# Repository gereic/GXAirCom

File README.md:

# GxAirCom

GxAircom aims to be a complete and open source implementation of the [FANET+ (Fanet + Flarm) protocol](https://github.com/3s1d/fanet-stm32/blob/master/Src/fanet/radio/protocol.txt) running on readily available cheap lora modules and interfacing with mobile phones via Bluetooth. It can also act as a Fanet ground station and broadcast recieved FANET information to [OGN](http://wiki.glidernet.org).

For information and documentation see:

- [The PDF quick guide](doc/20200908%20-%20GXAirCom%20-%20Quick%20Guide.pdf) and the [The PDF Documentation](doc/20200723%20-%20GXAirCom%20-%20A%20LoRa%20communication%20device%20for%20free%20flying.pdf)
- Further information can be found in [the wiki](https://github.com/gereic/GXAirCom/wiki) and [the docs folder](doc/). E.g.:
    - [The list of supported hardware](https://github.com/gereic/GXAirCom/wiki/Hardware-supported)
    - [The list of supported smartphone software](https://github.com/gereic/GXAirCom/wiki/Software)
    - [How to update the firmware](https://github.com/gereic/GXAirCom/wiki/Upgrading---updating-the-firmware-using-the-internal-web-interface-and-a-cellphone)
    - [See the video tutorials](https://github.com/gereic/GXAirCom/wiki/Video-Tutorials)

## ADS-L (SRD-860 M-Band) Support

GXAirCom implements the EASA **ADS-L 4 SRD-860** iConspicuity protocol (Issue 1 / Issue 2, December 2025).  
ADS-L lets non-certified aircraft broadcast and receive position data on a standardised EU frequency plan, independently of FLARM.

### Protocol overview

| Parameter | Value |
|---|---|
| Frequencies | 868.200 MHz and 868.400 MHz (M-Band), alternated per transmission |
| Modulation | 2-GFSK, 100 kbps chip rate (50 kbps net after Manchester) |
| Deviation | ±50 kHz |
| RX bandwidth | 125 kHz |
| Encoding | Software Manchester — G.E. Thomas convention (`0`→`10`, `1`→`01`) |
| Hardware Manchester | Disabled (`RegPacketConfig1 = 0x00`) |

### Packet structure (25 decoded bytes)

```
Byte  0      Length byte = 0x18 (24 bytes follow)
Byte  1      Network byte: Protocol=0, SigFlag=0, KeyIdx=0, ECM=0
Bytes 2–21   ADS-L Data (20 bytes) — XXTEA-scrambled
               Byte  2     Payload Type = 0x02 (Traffic / iConspicuity)
               Bytes 3–5   Sender address (24-bit, MSB first)
               Byte  6     AMT (6 bits, bits[7:2]) | Relay (bit 0)
               Bytes 7–21  iConspicuity payload (15 bytes = 120 bits)
Bytes 22–24  CRC-24 (big-endian, covers bytes 1–21)
```

On air the 25-byte packet is Manchester-encoded to **50 bytes**, transmitted after the sync word.

### iConspicuity payload bit layout (120 bits, MSB-first)

| Bits | Width | Field | Unit / notes |
|---|---|---|---|
| 0–5 | 6 | Timestamp | Quarter-seconds since UTC hour, mod 60 (0–59) |
| 6–7 | 2 | Flight State | 0=undefined, 1=ground, 2=airborne |
| 8–12 | 5 | Aircraft Category | 0=none … 13=UAS certified (EASA Issue 2 table) |
| 13–15 | 3 | Emergency Status | 0=none, 2=general, 3=medical … |
| 16–39 | 24 | Latitude | Signed, LSB = 1°/93 206 (~1.2 m) |
| 40–63 | 24 | Longitude | Signed, LSB = 1°/46 603 (~1.2 m at equator) |
| 64–71 | 8 | Ground Speed | Exp-unsigned N=6, unit 0.25 m/s |
| 72–85 | 14 | Altitude WGS-84 | Exp-unsigned N=12, +320 m offset |
| 86–94 | 9 | Vertical Rate | Exp-signed N=6, unit 0.125 m/s (sign in bit 8) |
| 95–103 | 9 | Ground Track | Cyclic, 360°/512 per LSB |
| 104–105 | 2 | SIL | Source Integrity Level |
| 106–107 | 2 | DAL | Design Assurance Level |
| 108–111 | 4 | NIC | Navigation Integrity Category |
| 112–114 | 3 | HFOM | Horizontal Figure of Merit |
| 115–116 | 2 | VFOM | Vertical Figure of Merit |
| 117–118 | 2 | NACv | Navigation Accuracy for Velocity |
| 119 | 1 | Reserved | Always 0 |

Non-certified devices transmit SIL=0, DAL=0 (conservative defaults per spec appendix).

### Scrambling — XXTEA

ADS-L Data (bytes 2–21, 20 bytes = 5 × uint32\_t LE words) is scrambled with **XXTEA**, 6 rounds, all-zero 128-bit key.  
This provides basic obfuscation but not cryptographic security (the spec acknowledges this).

### CRC-24

Same polynomial as Mode-S / ADS-B: **0xFFFA0480** (generator degree 24).  
The CRC is computed over 21 bytes (Network byte + XXTEA-encrypted ADS-L Data) and appended big-endian.

### Sync word

The radio sync word is a **6-byte Manchester-encoded** pattern derived from raw bytes `0xF5 0x72 0x4B`:

```
55 99 95 A6 9A 65
```

This 6-byte form matches the **OpenACE** and **SoftRF** on-air pattern.  
The leading `55 99` = Manchester(`0xF5`) acts as the explicit preamble byte required on SX1262 hardware (see [issue #210](https://github.com/gereic/GXAirCom/issues/210)).  
The spec-defined sync bytes `0x72 0x4B` are encoded as `95 A6 9A 65`.

| Chip | Sync config | SyncWordLength |
|---|---|---|
| SX1276 | `RegSyncConfig = 0x35` (SyncOn, SyncSize=6) | 6 bytes |
| SX1262 | SetPacketParams, 48 bits | 6 bytes written to register `0x06C0` |

### Address Mapping Table (AMT)

GXAirCom uses AMT = **8 (FANET)** by default. Other notable values: 5=ICAO, 6=FLARM, 7=OGN, 0=Random/Privacy.

### Interoperability

| System | Status |
|---|---|
| OpenACE | ✅ Compatible — same 6-byte sync, same packet structure |
| SoftRF (moshe-braner fork) | ✅ Compatible — same sync word pattern confirmed |
| OGN receivers | ✅ CRC-24 + packet structure matches Mode-S tooling |

Similar/ related projects are:

- The [SoftRF](https://github.com/lyusupov/SoftRF) project, which has wider hardware and protocol support, but implements only the subset of the FANET protocol that broadcasts and receives locations. It also cannot broadcast FANET and FLARM at the same time.
- The [Skytraxx FANET Source](https://github.com/3s1d/fanet-stm32). The original reference implementation of the FANET standard and upstream of the standard protocol specification and documentation.

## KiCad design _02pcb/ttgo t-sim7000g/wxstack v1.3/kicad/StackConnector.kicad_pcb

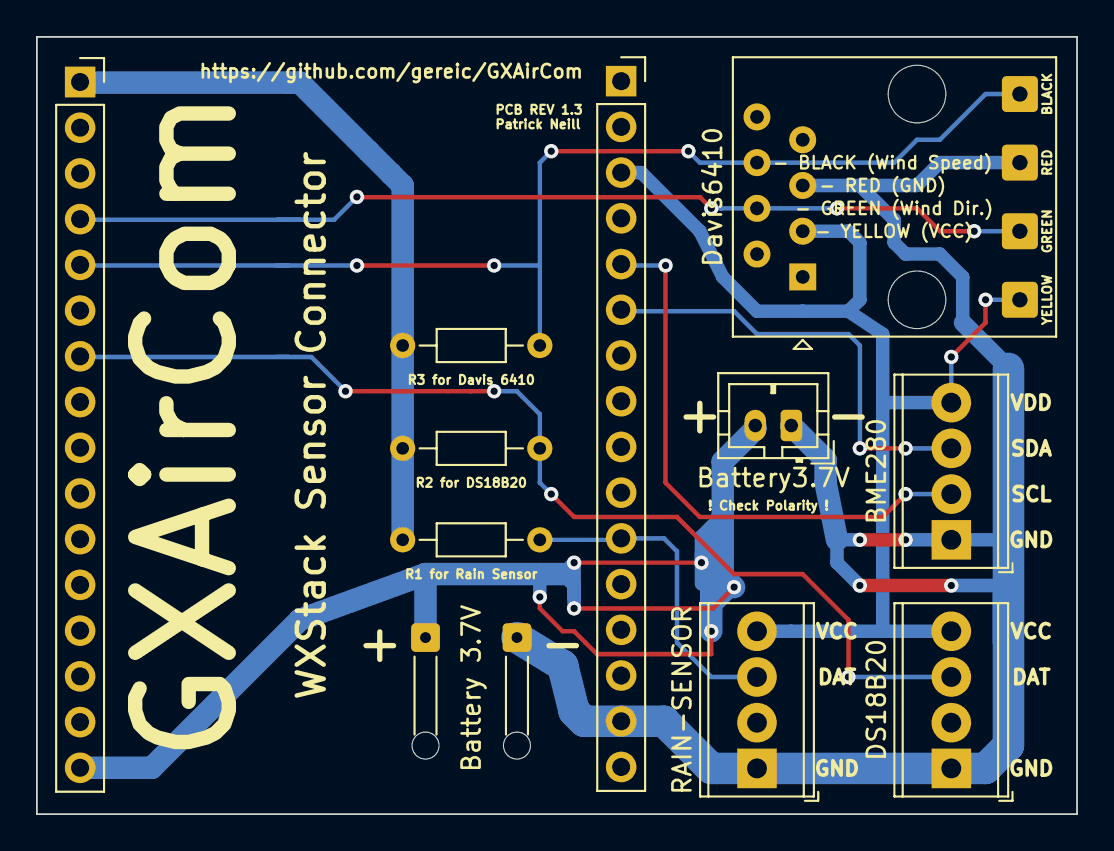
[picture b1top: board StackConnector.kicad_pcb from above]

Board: 2 copper layers, 57.8 x 43.2 mm, 16 parts (0 on the bottom side), 10 nets.

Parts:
BLACK: Conn_01x01; SolderWire-0.25sqmm_1x01_D0.65mm_OD2mm
BME280: Screw_Terminal_01x04; TerminalBlock_Phoenix_MPT-0,5-4-2.54_1x04_P2.54mm_Horizontal
Battery3.7V: Conn_01x02; JST_PH_B2B-PH-K_1x02_P2.00mm_Vertical
DS18B20: Screw_Terminal_01x04; TerminalBlock_Phoenix_MPT-0,5-4-2.54_1x04_P2.54mm_Horizontal
Davis6410: RJ45; RJ45_Amphenol_54602-x08_Horizontal
GREEN: Conn_01x01; SolderWire-0.25sqmm_1x01_D0.65mm_OD2mm
J1, J2: Conn_01x16_Female; PinSocket_1x16_P2.54mm_Vertical
J3, J4: Conn_01x01; SolderWire-0.1sqmm_1x01_D0.4mm_OD1mm_Relief
R1: R1; R_Axial_DIN0204_L3.6mm_D1.6mm_P7.62mm_Horizontal
R2: R2; R_Axial_DIN0204_L3.6mm_D1.6mm_P7.62mm_Horizontal
R3: R3; R_Axial_DIN0204_L3.6mm_D1.6mm_P7.62mm_Horizontal
RAIN-SENSOR: Screw_Terminal_01x04; TerminalBlock_Phoenix_MPT-0,5-4-2.54_1x04_P2.54mm_Horizontal
RED: Conn_01x01; SolderWire-0.25sqmm_1x01_D0.65mm_OD2mm
YELLOW: Conn_01x01; SolderWire-0.25sqmm_1x01_D0.65mm_OD2mm

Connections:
+3.3VP: J1.1, R1.1, R2.1, R3.1
+3V3: BME280.4, DS18B20.4, Davis6410.3, J2.3, RAIN-SENSOR.4, YELLOW.1
GND1: BME280.1, Battery3.7V.1, DS18B20.1, Davis6410.5, J2.15, J3.1, RAIN-SENSOR.1, RED.1
unnamed: BLACK.1, Davis6410.6, J1.5, R3.2
unnamed: BME280.2, J2.5
unnamed: BME280.3, J2.6
unnamed: Battery3.7V.2, J1.16, J4.1
unnamed: DS18B20.3, J1.7, R2.2
unnamed: Davis6410.4, GREEN.1, J1.4
unnamed: J2.11, R1.2, RAIN-SENSOR.3

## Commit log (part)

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2021-01-05 added accelerometer for better vario added temp-offset for vario added config-button for ublox-GPS --> only GPGGA and GPRMC will sent --> much less traffic added new configuration extpw (external pow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
2021-01-06 !!!! ATTENTION !!! PIN Buzzer changed from 0 to 25 added restriction for ground-station name in webinterface fanet-weather-data will also be forwarded to OGN. --> https://www.gliderradar.com/
2021-01-09 new Lib for bluetooth-Le
2021-01-10 Weather
2021-01-10 weather 2
2021-01-13 V3.2.1 added FANET-Pin (for further control of device over FANET-MSG's) added more data for OGN (batt-voltage, pressure, temp, humidity) added "#FNG (0..F)\n" message for setting Ground-tracking type
2021-01-15 spiff
2021-01-18 added multi-ble-support (for example, connect with XCTrack and at same time also with XCGuide)
2021-01-26 V4.0.0 only 4 different Firmwares anymore, cause of new bluetooth-lib, it can do all variations in one Firmwares added system-commands for changing mode, name, type, read Version via serial, and blue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
2021-01-28 added support, to send system-command via FANET msg hat following format: PXXXX#SYC .... XXXX ... fanet-pin from settings after that send normal #SYC-msg useful, to switch on WIFI or to get Version.
2021-01-28 moved old firmwares
2021-01-29 Bugfix: neighbours.html had no function anymore
2021-01-31 stack connector pcb for t-sim7000g
    stacking connector pcb for connecting weather sensors to ttgo t-sim7000g
2021-02-01 bugfix neighbours
2021-02-04 bugfix sending tracking-data to OGN weather-data, try to read BME 5 times in case, values are not valid (outside range)
2021-02-10 V4.3.4 bugfix when switching to OLED-Display-Type
2021-02-11 WIndDir AVG factor - configurable - default
2021-02-11 v4.4.0 added new lib acebutton for using buttons of boards (click and long-press) new Feature, prg-Button used on Heltec-Board for Power-Off and screen-switch
2021-02-11 save avgFactor - default 17
2021-03-03 v4.6.0 added view for settings (basic, advanced, expert) added avgfactor for sending weather-data added adjustable intervall for upload weather-data to WU
2021-03-07 changed readme.txt
2021-03-08 FANET upload interval in config file
2021-03-08 Bugfix in windgust-calculation
2021-03-12 changed Pin Buzzer
2021-03-13 v4.7.0 New Feature: send and receive Fanet and Legacy (switching between 1.9sec Legacy-Mode 3sec. Fanet-Mode) PinBuzzer for TTGO T-Beam V0.7 and Heltec changed from 0 to 25 added Log-Output for weath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
2021-03-14 v4.7.1 Bugfix Legacy-Rx
2021-03-19 v4.8.0 support for T-Beam with SX1262-Chip (ATTENTION --> at the moment no E-Ink for this board) automatic detection of T-Beam with SX1262-Chip Bugfix Legacy-speeed Bugfix Legacy-vertial-speed Bugfix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
2021-03-21 v4.8.2 Changed Timing for simultaneoulsy Fanet-Legacy-Mode added Info in neighbours.html, if message was a FANET or LEGACY
2021-03-28 v4.8.4 Fix Bluetooth-connection crashes ESP32 --> implemented new nimble v1.20 Stopped ble-function on firmware-update, otherwise esp can crash
2021-04-06 added Testroutine for Legacy-Data
2021-04-15 test-version with sx1262 and Legacy-rx
2021-04-18 Bugfix in mode Legacy_RX/TX added Counter for Legacy-rx/tx
2021-05-02 v4.7.1 added support for Waveshare 2.9 E-Ink V2 (see Label on Backside of E-Ink) added average for fuel-sensor
2021-05-06 Change links to work with githubs renderer
2021-05-09 created new Version
2021-05-13 changed Text LXPW to LXWP0
2021-06-13 v4.10.1 time for autocalibration of sx1276 changed 1sek. --> 5min.
2021-06-24 added support for remote-online-update via FANET-Command
2021-07-10 new systemcommands over bluetooth #SYC RFMODE? get RF-Mode #SYC RFMODE=11 set RF-Mode Bit 0 .... FANET Receive enable Bit 1 .... FANET Transmit enable Bit 2 .... Legacy Receive enable Bit 3 .... Lega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
2021-07-12 created new binarys
2021-08-02 v4.11.2 Bugfix in ble-command #SYC RFMODE=
2021-08-13 added support for E-Ink on ground-Station (T-Sim7000) added battery-life-power-option added turning for E-Ink in ground-station-mode
2021-09-05 added factory-reset for SIM7000
2021-10-10 updated the WXStack PCB and added new PCB and bill of materials for Phoenix Contact ECS case build
2021-10-23 added setting to get GPS-Position for ground-station (T-Sim7000)
2021-11-02 merging local init development for igc to sd logger feature
2021-11-04 change status.GPS_Date, auto incrememnt igc filenames to manage multiple igc for single day, write headers
2021-11-05 updating igc headers and set gpio for gps tx to 39 to avoid conflicts for board T3 lilygo
2021-11-05 adding coordinates to B record igc file
2021-11-06 fix table header to download
2021-11-11 adding taskLogger handler to manage soStopLogger when power off (when low battery close igc file before power off)
2021-11-12 fix battery adcVoltageMultiplier for TTGO T3 v2.1.6.1 to 3.5 and adding temperature and vbatt voltage to oled display to check overheating while charging
2021-11-13 changed Baro, SX1276 rewrite of Code
2021-11-13 addgin gps date time to wenhelper when fix is done
2021-11-18 synced pull-request for ttgo-lora32-v1 IGC-Logger
2021-11-21 Code Cleanup
2021-11-29 E-Ink for T-Beam SX1262 is now supported (but only in Air-Mode). (some Pins need to be changed) Updated E-Ink-Lib for supporting Waveshare 2.9 V2-Modules
2021-12-25 added first draft of MQTT-connection
2022-01-08 bugfix receiving FANET (CRC was not checked)
2022-02-18 Using GPS for Ground-Station (only active, when lat and lon in settings 0) Added GPS-Output for Ground-Station
2022-02-18 changed calibration of ACC
2022-03-06 BLE improvements
2022-05-14 added reconnect on station disconnected
2022-05-28 changed Legacy
2022-07-08 new Flarm-integration for sending compatible Flarm-packages
2022-07-28 Necessary updates for recent arduino/esp32 libs
    Including an update for the Onewire lib.
2022-09-03 added menu to select network preference (LTE-M, NB-IOT)
    added menu to select network preference (LTE-M, NB-IOT)
2022-09-07 Added Adjustable CPU-Speed (Range 240Mhz - 80Mhz)
2022-09-23 Fix Tx20.h include filename
    Fixes #106
2022-09-23 Build plaforms as single jobs
2022-10-14 set Refresh of NTP-Time every 30min. instead of once per day
2022-10-20 force platform to espressif32@3.4.0
2022-10-20 $LK8EX1 nmea sentence : send battery level in percentage instead of voltage
2022-10-21 Fixed Temp-Correction for GY-86-Board
2022-10-22 psRam recompiled
2022-11-15 use FreeRTOS `QueueHandle_t` to exchange data from main task to Bluetooth task
2022-11-18 init to not send winddir and windspeed
2022-11-19 Add partitions and pio config for 8mb/16mb boards
    Targeting mainly the heltec lora32 and lilygo t-sim7000 board with 16MB
    flash.
2022-11-19 Remove trailing spaces from pio config
2022-12-04 added LBT-Feature for FANET added websites in Flash no spiffs needed anymore
2022-12-23 Add ADS1X15 Library
2022-12-23 Measure vref instead of using a setting.
    Various other fixes, working implementation so far.
2022-12-23 disable listSPffFiles again
2022-12-23 Add new versions of stripped files/website.h
2022-12-27 added sendmessages.html
2022-12-27 send weather-data to wu and wi only if we are a ground-station
2022-12-28 added support for ADS1015 and Peet Bros weather-station set MQTT timestamp to ISO8601 send MQTT weather-data according to existing sensors
2022-12-30 added worldwide FANET-frequencys added worldwide Flarm-frequencys Flarm outside europe is only working with GPS (and PPS-Signal like TTGO T-Beam), because of frequency-hoping (not well tested yed (ou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
2023-01-17 working fix on T3
2023-01-20 lower freehep limit for logger
2023-01-21 logger folders and igc sha256
2023-01-21 secret SHAPRIVATEKEY value
2023-01-22 igclogs web page update
2023-01-22 igc web page update js script
2023-01-22 adding igc_key.h with random key to have code working
2023-01-23 secret igc_key and pre-script to create h file
2023-01-23 Add support for barometer BMP3xx
    Add support for Bosch Sensotec BMP380 and BMP390 barometer\nUses Adafruit library
2023-01-24 igclogger web page sorted tracks by date descending
2023-02-16 added sendmessage menuepoint in in expert settings
2023-03-02 adding references to the new env
2023-03-22 switch off SSL, because only 2 are supported on SIM7000
2023-07-05 Implement XPowersLib for AXP management
2023-07-15 seperated oled to another task sync i2c with mutex baro on S3Core is working now changed from axp-lib to xpowerlib for all PMU
2023-07-15 Fix for E-Ink T-Beam
2023-07-18 Removed empty else
2023-07-23 - Set GPS to 5Hz, enable Galileo and dynamicMode 2G - Request Configuration using $PGXCF,? - Allow setting of (part of) configuration using $PGXCF $PGXCF,<version>,<eMode>,<eOutputVario>,<output Fane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
2023-07-23 Clarification in committed
2023-07-23 Upgrade to new ublox library Removed specific config commands and replaced with nmeaCommands Not setting some constallations is ok to continue.
2023-08-04 Fix potential buffer overflow while reading NMeaSerial Fix issue when seeing 0xff characters is passthrough GPS data Avoid calling available() on serial twice
2023-08-06 changed Updater
2023-09-04 Ignore missing files in data dir on remove
2023-09-09 Implement rain handling for holfuy
2023-09-13 fixed deep-sleep for sim7000 added offset for sunset and sunrise
2023-09-22 Bugfix when updating via MQTT Changed Compile-DT to display in ISO8601-format added version, buildDate, sdkVersion, img in mqtt
2023-10-03 changed parity-calc on Flarm added GPS-configuration for Quetel-chips
2023-10-13 added option for disable wifi complete at startup min. frequency of board without wifi and bluetooth enabled is 20Mhz now.
2023-10-15 added mqtt command to change cpu frequency set wifi tx-power to maximum
2023-12-11 added Heltec Wireless Stick Lite v3
2023-12-20 created spiffs
2024-03-13 trying adding heltec v3 Board
2024-03-15 changed WU and Windy-Upload to https Only working with Wifi-Connection
2024-03-17 Updating web content
2024-03-17 Adding the SparkFun Weather Meter to the Weather class
2024-03-26 added sending received weather-stations to MQTT-broker
2024-04-11 added onewire-pin for wireless-stick v3
2024-05-12 disabled 32K output on RTC
2024-05-19 added new Version of wesocket-server Bugfix: webinterface is not working in AP-Mode
2024-07-11 Bugfix Peet Bros Anemometer
2024-08-02 changed peet-bros
2024-08-12 changed RTC to pointer so that we don't need to do wire.begin always
2024-08-27 changed some settings visibility
2024-08-28 added some logging
2024-10-05 enabled Flarm again.
2024-10-26 changed settings for GPS
2024-11-02 set new NTP-Client
2024-11-03 use github actions to create binaries
2024-11-03 remove non-Stratux targets
2024-11-03 simplifications
2024-11-10 changed GPS-configuration for Quectel GPS
2024-12-21 recoded peet-bros-anemometer ... ready for testing in real conditions
2024-12-25 Bugfix on Peet-Bros-Anemometer
2025-01-05 add Log
2025-02-01 added direction-filter for peet-pros
2025-02-15 Bugfix von compile-date
2025-02-16 removed temporary mqtt-messages
2025-02-22 PCB and parts list for Heltec Stick Lite V3
    solar, four 18650, RTC, LTE modem and Takeshi mast mount case
2025-03-09 created new Version 8.1.1 added BME380 Fix AddressType in PFLAA message
2025-03-13 added support for Heltec Vision Master E290
    added support for Heltec Vision Master E290
    fixed createheaderfile for windows
2025-03-15 Handle PFLAC radioid request
2025-03-23 added frequency-correction added GPGSA-messages
2025-04-13 HeltecV3 with Sim800l
2025-04-25 Add FANET commands
2025-05-04 added ChanSeparation
2025-05-14 fixed Bug on Boards without PPS-Pin
2025-07-16 Bugfix for New Zealand Flarm receiving
2025-07-17 added more SYC-command ans description in /bin
2025-07-27 Bugfix receiving Flarm in NZ
2025-08-05 added WS90 anemometer with cc1101 rf-module
2025-08-13 added code for WS85-rf
2025-09-07 Bugfix for Peet-Bros and Misol
2025-09-29 added Info for received data for forwarded weather-stations
2025-11-09 Porting Heltech Wireless Tracker with new TFT display handler and wifi AP configuration options
2026-01-03 Firmware for Flarm-Debug
2026-01-03 removed check for some unknown bits in Flarm-Message
2026-02-25 Bump minimatch from 3.1.2 to 3.1.4 in /bundle
    Bumps [minimatch](https://github.com/isaacs/minimatch) from 3.1.2 to 3.1.4.
    - [Changelog](https://github.com/isaacs/minimatch/blob/main/changelog.md)
    - [Commits](https://github.com/isaacs/minimatch/compare/v3.1.2...v3.1.4)
    ---
    updated-dependencies:
    - dependency-name: minimatch
